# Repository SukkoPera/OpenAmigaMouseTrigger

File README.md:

# OpenAmigaMouseTrigger
OpenAmigaMouseTrigger is an Open Hardware PCB that allows using the state of the mouse buttons at power-up of an Amiga computer to trigger features of other boards, instead of using physical switches. This is mainly useful for controlling a [Kickstart Switcher](https://github.com/SukkoPera/OpenKickstartSwitcher) or a [Drive Switcher](https://github.com/SukkoPera/OpenAmigaDriveSwitcher).

### Summary
If you install a Kickstart Switcher in your Amiga, you might not want to drill a hole in its venerable case in order to install a switch to select the Kickstart of your choice. Back in the day, it was common to do your selection by holding or not the left mouse button at power-up. OpenAmigaMouseTrigger is a reimplementation of this mechanism on a small isolated board, so that you can use it to trigger anything you want, and not be limited to Kickstarts or even to Amiga computers.

OpenAmigaMouseTrigger also features a second channel, so you can generate up to four different signal combinations.

### Assembly
Solder all components to the board. No particular order is recommended, but starting with the smaller components might be a good idea.

### Installation
Connect the signals you want to sample at power-up to I1 and I2. Connect the signals you want to drive to O1 and O2. Install R1 and R2 if the input signal needs pull-up resistors.

OpenAmigaMouseTrigger was designed to work with [OpenKickstartSwitcher](https://github.com/SukkoPera/OpenKickstartSwitcher). You can also use it in other scenarios, but the default component values were tuned for this case. While it would be great to use both mouse buttons as input signals, [the right mouse button is not usable for this](https://www.dropbox.com/s/n4spcituqtnby74/MouseSwitcherFailSmall.png), probably because of how the Amiga sampling circuit was designed. I suggest to use the port 2 joystick fire button as the second selection signal. This is ideal if you put DiagROM + Kickstart 1.3 + Kickstart 3.1 on your OpenKickstartSwitcher, since you won't use DiagROM too often, and you'll be able to select the other two ROMs with the left mouse button.
If your mouse buttons already are used for boot menus or similar, you can use port 2 joystick directions instead. No movement of the joystick will launch your default ROM, you'll be able to select the other two ROMs by holding your joystick in the direction of your choice. Note that to be able to choose between four ROMs, the fourth direction will have to be diagonal, so you have to pick two adjacent directions . Signal 1 is Up, signal 2 is Down, signal 3 is Left, and signal 4 is Right, see image for reference 

R4 is a bleeder resistor used to discharge C1 quickly when power is removed, be sure to allow at least 4-5 seconds before turning your system back on.

If you use OpenAmigaMouseTrigger in a different scenario, you might want to alter the sampling delay at power-up. This can be done by changing the values of C1 and R3, which form a simple RC network which drives the flip-flip clock signal. The default values will yield a delay or around 50 us, which is quite good for the Amiga (it has a power-on reset pulse after about 100 us) but note that actual capacitor values may differ a lot from the nominal capacity, even 20%, so you might need to do some tweaking. You might also want to experiment with different values of R4, if your C1 has a largely different capacity.

### License
OpenAmigaMouseTrigger is Open Hardware. If you make any modifications to the board, please contribute them back.

### Support the Project
If you want to get some boards manufactured, you can get them from PCBWay through this link:

You get my gratitude and cheap, professionally-made and good quality PCBs, I get some credit that will help with this and [other projects](https://www.pcbway.com/project/member/shareproject/?bmbid=41100). You won't even have to worry about the various PCB options, it's all pre-configured for you!

Also, if you still have to register, [you can use this link](https://www.pcbway.com/setinvite.aspx?inviteid=41100) to get some bonus initial credit (and yield me some more).

You can also buy me a coffee if you want:

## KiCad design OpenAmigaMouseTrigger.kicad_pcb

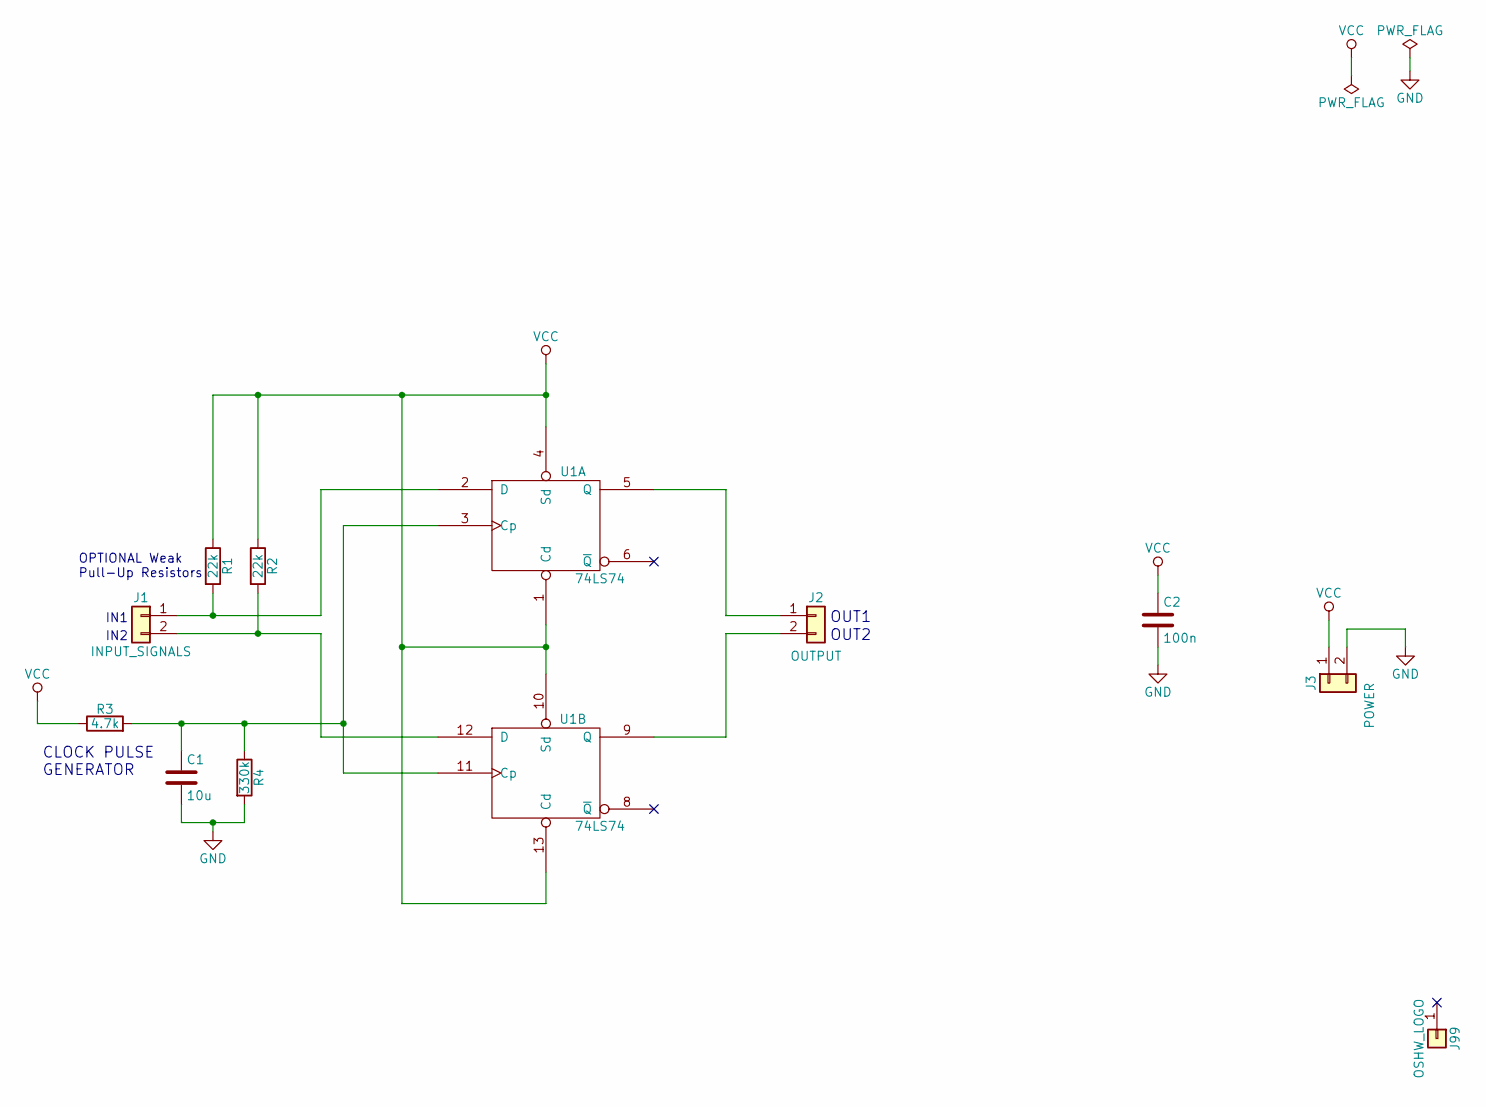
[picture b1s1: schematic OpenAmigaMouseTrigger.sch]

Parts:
C1: 10u; CP_Radial_D5.0mm_P2.00mm
C2: 100n; C_Disc_D7.0mm_W2.5mm_P5.00mm
J1: INPUT_SIGNALS; LoosePads-2
J2: OUTPUT; LoosePads-2
J3: POWER; LoosePads-2
J99: OSHW_LOGO; Logo_copper_OSHW_6x6mm
R1, R2: 22k; R_Axial_DIN0207_L6.3mm_D2.5mm_P10.16mm_Horizontal
R3: 4.7k; R_Axial_DIN0207_L6.3mm_D2.5mm_P10.16mm_Horizontal
R4: 330k; R_Axial_DIN0207_L6.3mm_D2.5mm_P10.16mm_Horizontal
U1: 74LS74; DIP-14_W7.62mm

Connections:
GND: C1.2, C2.2, J3.2, R4.2, U1.7 (GND)
unnamed: C1.1, R3.2, R4.1, U1.3 (Cp), U1.11 (Cp)
unnamed: J1.1, R1.2, U1.2 (D)
unnamed: J1.2, R2.2, U1.12 (D)
unnamed: J2.1, U1.5 (Q)
unnamed: J2.2, U1.9 (Q)
VCC: C2.1, J3.1, R1.1, R2.1, R3.1, U1.1 (Cd), U1.4 (Sd), U1.10 (Sd), U1.13 (Cd), U1.14 (VCC)

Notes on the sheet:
IN1
IN2
CLOCK PULSE GENERATOR
OPTIONAL Weak Pull-Up Resistors
OUT1
OUT2

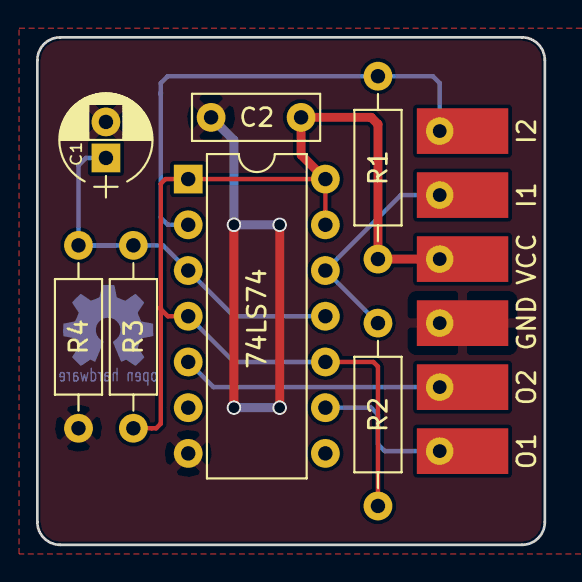
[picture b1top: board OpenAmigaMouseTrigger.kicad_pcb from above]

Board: 2 copper layers, 28.2 x 28.2 mm, 11 parts (1 on the bottom side), 7 nets.

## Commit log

2017-12-22 Round corners, stitch grounds, routing adjustments
2018-01-07 Final touches for V1
2018-01-07 Add README
2018-05-29 V2 is ready
2018-05-29 Fix silkscreen URL
2018-06-24 Improve README
2020-06-09 Updated readme with alternative trigger singals
2020-06-09 Added image for alternative trigger signals
2020-06-10 changed image url
2020-06-10 Updated README with alternative trigger signals
    Added image that shows the alternative trigger signals
2026-02-13 Revise support section and add donation link
    Updated the support section to improve clarity and added a 'Buy Me a Coffee' option.
